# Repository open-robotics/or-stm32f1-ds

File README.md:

OR-STM32F1-DS
=============

Open Robotics controller based on STM32F103VC chip.

Feauters
--------

* 20 servo control outputs
* 8 RoboGPIO with ADC option
* 8 RoboGPIO with servo option
* Onboard dual channel motor H-dirver
* RoboMD2 for additional external motor driver
* Onboard USB
* Separated I<sup>2</sup>C in RoboBUS and RoboI2C
* 2 quadrature encoder inputs

Connectors
----------

* 20 Servo
* 16 RoboGPIO
* 2 brush motor
* 1 RoboBUS
* 1 RoboMD2
* 1 RoboI2C
* 1 USB

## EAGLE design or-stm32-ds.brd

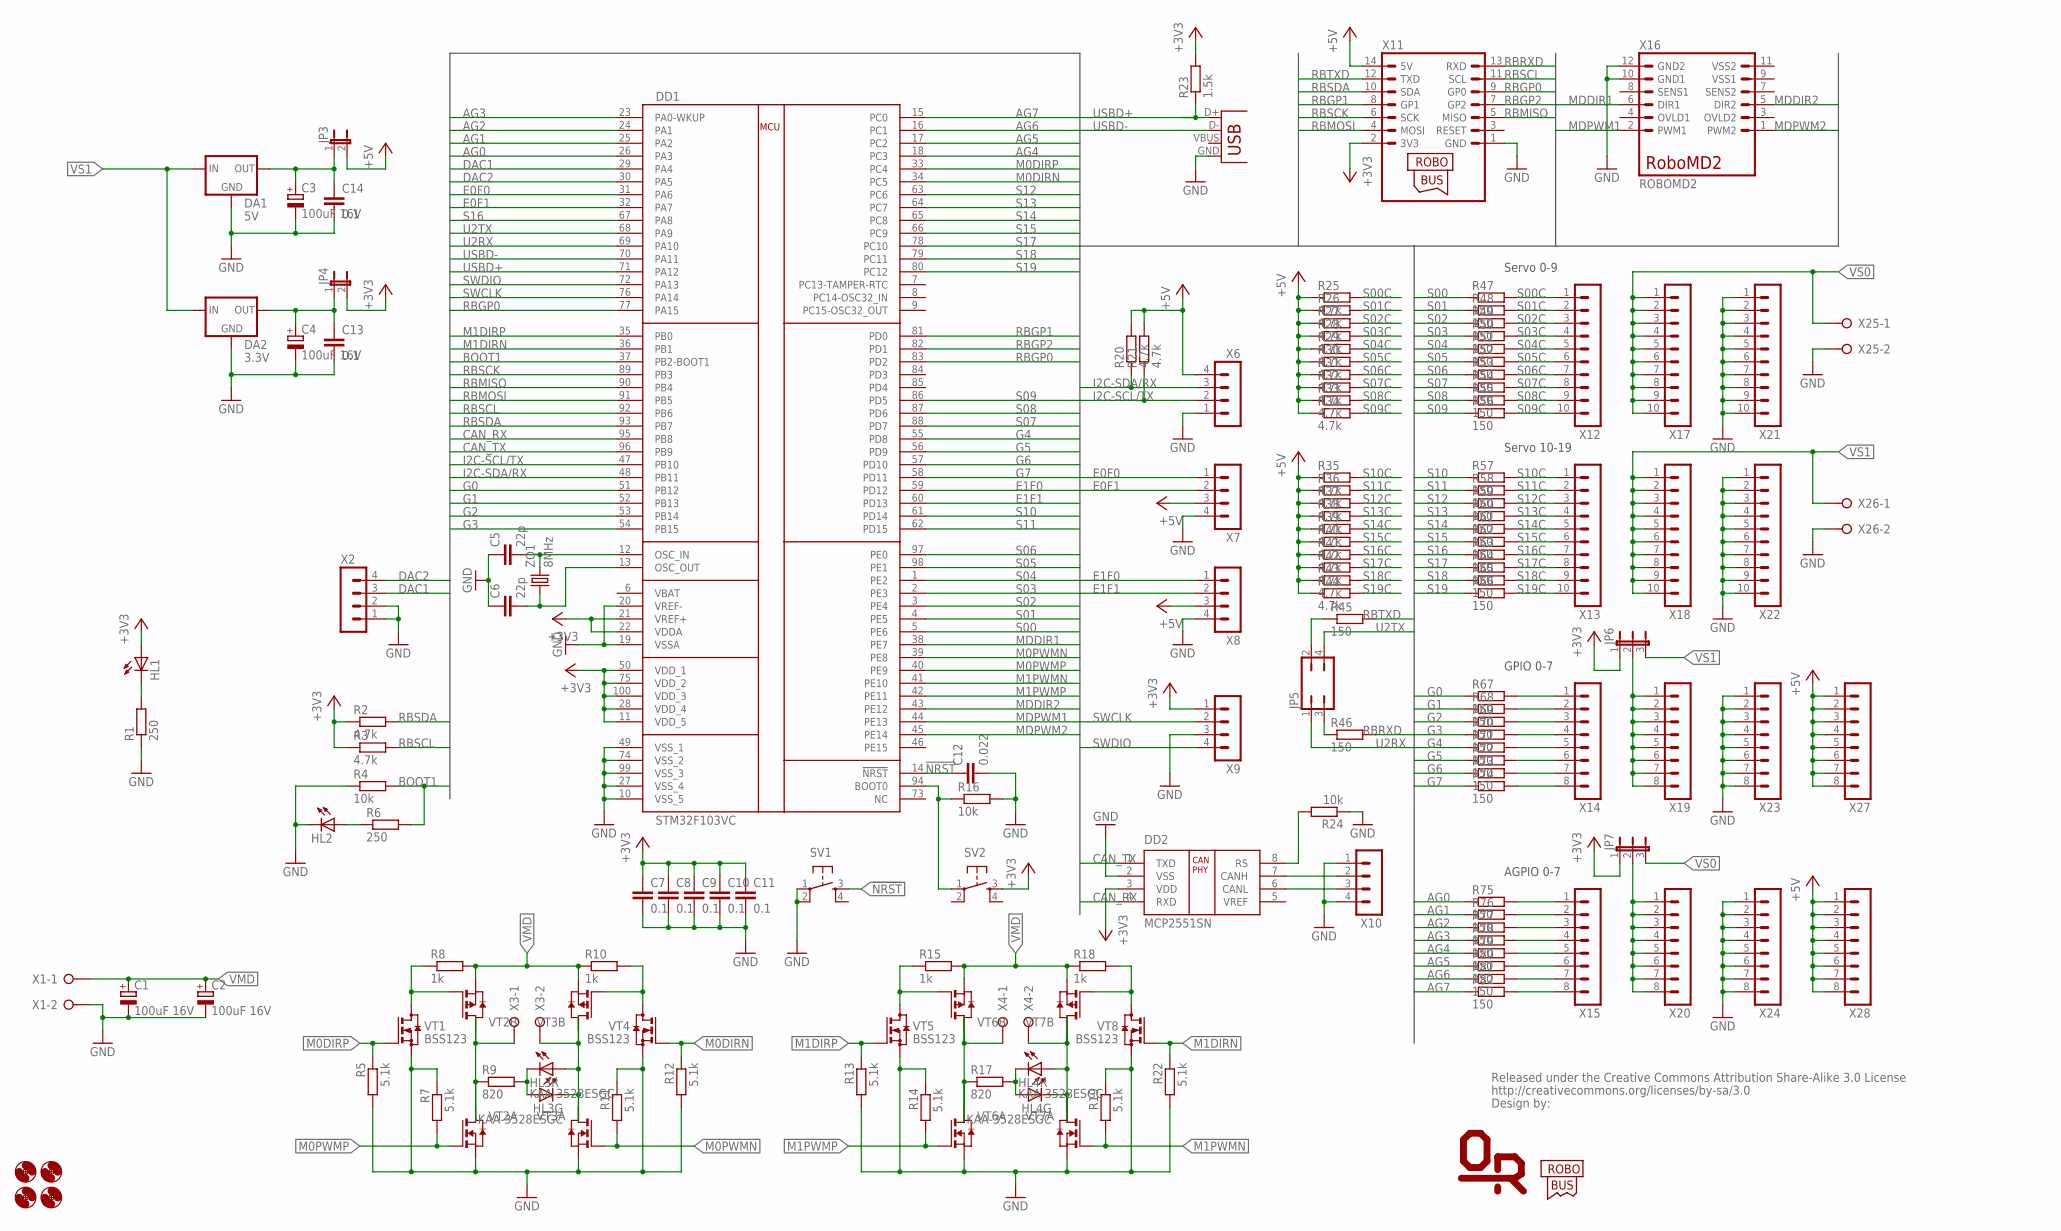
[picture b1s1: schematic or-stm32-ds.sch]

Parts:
C1, C2, C3, C4: 100uF 16V; E3,5-8
C5, C6: 22p; C0603
C7, C8, C9, C10, C11, C13, C14: 0.1; C0603
C12: 0.022; C0603
DA1: 5V; SOT223
DA2: 3.3V; SOT223
DD1: STM32F103VC; LQFP100
DD2: MCP2551SN; SO-08
H1, H2, H3, H4: MOUNT-HOLE3.2; 3,2
HL1, HL2: LEDCHIP-LED0805; CHIP-LED0805
HL3, HL4: KAA-3528ESGC; KA-3528
JP3, JP4: JP1E; JP1
JP5: JP2Q
JP6, JP7: JP2E; JP2
R1, R6: 250; R0603
R2, R3, R20, R21, R25, R26, R27, R28, R29, R30, R31, R32, R33, R34, R35, R36, R37, R38, R39, R40, R41, R42, R43, R44: 4.7k; R0603
R4, R16, R24: 10k; R0603
R5, R7, R11, R12, R13, R14, R19, R22: 5.1k; R0603
R8, R10, R15, R18: 1k; R0603
R9, R17: 820; R0603
R23: 1.5k; R0603
R45, R46, R47, R48, R49, R50, R51, R52, R53, R54, R55, R56, R57, R58, R59, R60, R61, R62, R63, R64, R65, R66, R67, R68, R69, R70, R71, R72, R73, R74, R75, R76, R77, R78, R79, R80, R81, R82: 150; R0603
SV1, SV2: TAC_SWITCHSMD; TACTILE_SWITCH_SMD
U$1: CREATIVE_COMMONS_BY-SA; CC-BY-SA-6MM
U$2: ORLOGO
U$3: ROBOBUS_LOGO
VT1, VT4, VT5, VT8: BSS123; SOT23
VT2, VT3, VT6, VT7: PN_MOSFET-SO8; SO8
X1, X3, X4: HT396R-02P
X2, X9: MA04-11.27MM; 1X04-1.27MM
X5: USBSMD; USB-MINIB
X6, X7, X8, X10: MA04-1
X11: ROBOBUSR; ML14L
X12, X13, X17, X18, X21, X22: MA10-1
X14, X15, X19, X20, X23, X24, X27, X28: MA08-1
X16: ROBOMD2; ML12
X25, X26: W237-02P; W237-132
ZQ1: 8MHz; HC49U-V

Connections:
!NRST: C12.1, DD1.14 (!NRST), SV1.3
+3V3: C7.1, C8.1, C9.1, C10.1, C11.1, DD1.11 (VDD_5), DD1.21 (VREF+), DD1.22 (VDDA), DD1.28 (VDD_4), DD1.50 (VDD_1), DD1.75 (VDD_2), DD1.100 (VDD_3), DD2.3 (VDD), HL1.A, JP4.2, JP6.1, JP7.1, R2.1, R3.1, R23.2, SV2.3, X9.1, X11.2 (3V3)
+5V: JP3.2, R20.2, R21.2, R25.1, R26.1, R27.1, R28.1, R29.1, R30.1, R31.1, R32.1, R33.1, R34.1, R35.1, R36.1, R37.1, R38.1, R39.1, R40.1, R41.1, R42.1, R43.1, R44.1, X6.4, X7.3, X8.3, X11.14 (5V), X27.1, X27.2, X27.3, X27.4, X27.5, X27.6, X27.7, X27.8, X28.1, X28.2, X28.3, X28.4, X28.5, X28.6, X28.7, X28.8
AG0: DD1.26 (PA3), R75.1
AG0C: R75.2, X15.1
AG1: DD1.25 (PA2), R76.1
AG1C: R76.2, X15.2
AG2: DD1.24 (PA1), R77.1
AG2C: R77.2, X15.3
AG3: DD1.23 (PA0-WKUP), R78.1
AG3C: R78.2, X15.4
AG4: DD1.18 (PC3), R79.1
AG4C: R79.2, X15.5
AG5: DD1.17 (PC2), R80.1
AG5C: R80.2, X15.6
AG6: DD1.16 (PC1), R81.1
AG6C: R81.2, X15.7
AG7: DD1.15 (PC0), R82.1
AG7C: R82.2, X15.8
BOOT0: DD1.94 (BOOT0), R16.1, SV2.1
BOOT1: DD1.37 (PB2-BOOT1), R4.2, R6.2
CANH: DD2.7 (CANH), X10.2
CANL: DD2.6 (CANL), X10.3
CANRS: DD2.8 (RS), R24.2
CAN_RX: DD1.95 (PB8), DD2.4 (RXD)
CAN_TX: DD1.96 (PB9), DD2.1 (TXD)
DAC1: DD1.29 (PA4), X2.3
DAC2: DD1.30 (PA5), X2.4
E0F0: DD1.31 (PA6), X7.1
E0F1: DD1.32 (PA7), X7.2
E1F0: DD1.59 (PD12), X8.1
E1F1: DD1.60 (PD13), X8.2
G0: DD1.51 (PB12), R67.1
G0C: R67.2, X14.1
G1: DD1.52 (PB13), R68.1
G1C: R68.2, X14.2
G2: DD1.53 (PB14), R69.1
G2C: R69.2, X14.3
G3: DD1.54 (PB15), R70.1
G3C: R70.2, X14.4
G4: DD1.55 (PD8), R71.1
G4C: R71.2, X14.5
G5: DD1.56 (PD9), R72.1
G5C: R72.2, X14.6
G6: DD1.57 (PD10), R73.1
G6C: R73.2, X14.7
G7: DD1.58 (PD11), R74.1
G7C: R74.2, X14.8
GND: C1.-, C2.-, C3.-, C4.-, C5.1, C6.1, C7.2, C8.2, C9.2, C10.2, C11.2, C12.2, C13.2, C14.2, DA1.1 (GND), DA2.1 (GND), DD1.10 (VSS_5), DD1.19 (VSSA), DD1.20 (VREF-), DD1.27 (VSS_4), DD1.49 (VSS_1), DD1.74 (VSS_2), DD1.99 (VSS_3), DD2.2 (VSS), HL2.C, R1.1, R4.1, R5.2, R7.1, R11.1, R12.2, R13.2, R14.1, R16.2, R19.1, R22.2, R24.1, SV1.1, SV1.2, VT1.2 (S), VT2.1 (S), VT3.1 (S), VT4.2 (S), VT5.2 (S), VT6.1 (S), VT7.1 (S), VT8.2 (S), X1.2, X2.1, X2.2, X5.GND, X6.1, X7.4, X8.4, X9.3, X10.1, X10.4, X11.1 (GND), X16.10 (GND1), X16.12 (GND2), X21.1, X21.2, X21.3, X21.4, X21.5, X21.6, X21.7, X21.8, X21.9, X21.10, X22.1, X22.2, X22.3, X22.4, X22.5, X22.6, X22.7, X22.8, X22.9, X22.10, X23.1, X23.2, X23.3, X23.4, X23.5, X23.6, X23.7, X23.8, X24.1, X24.2, X24.3, X24.4, X24.5, X24.6, X24.7, X24.8, X25.2, X26.2
GPVCC: JP6.2, X19.1, X19.2, X19.3, X19.4, X19.5, X19.6, X19.7, X19.8
I2C-SCL/TX: DD1.47 (PB10), R21.1, X6.2
I2C-SDA/RX: DD1.48 (PB11), R20.1, X6.3
M0C+: R9.1, VT2.5 (D), VT2.6 (D2), VT2.7 (D), VT2.8 (D2), X3.1
M0C+1: R17.1, VT6.5 (D), VT6.6 (D2), VT6.7 (D), VT6.8 (D2), X4.1
M0C-: HL3.2 (A), HL3.3 (C), VT3.5 (D), VT3.6 (D2), VT3.7 (D), VT3.8 (D2), X3.2
M0C-1: HL4.2 (A), HL4.3 (C), VT7.5 (D), VT7.6 (D2), VT7.7 (D), VT7.8 (D2), X4.2
M0DIRN: DD1.34 (PC5), R12.1, VT4.1 (G)
M0DIRP: DD1.33 (PC4), R5.1, VT1.1 (G)
M0PWMN: DD1.39 (PE8), R11.2, VT3.2 (G)
M0PWMP: DD1.40 (PE9), R7.2, VT2.2 (G)
M1DIRN: DD1.36 (PB1), R22.1, VT8.1 (G)
M1DIRP: DD1.35 (PB0), R13.1, VT5.1 (G)
M1PWMN: DD1.41 (PE10), R19.2, VT7.2 (G)
M1PWMP: DD1.42 (PE11), R14.2, VT6.2 (G)
MDDIR1: DD1.38 (PE7), X16.6 (DIR1)
MDDIR2: DD1.43 (PE12), X16.5 (DIR2)
MDPWM1: DD1.44 (PE13), X16.2 (PWM1)
MDPWM2: DD1.45 (PE14), X16.1 (PWM2)
unnamed: JP5.3, R46.1
unnamed: C5.2, DD1.12 (OSC_IN), ZQ1.2
unnamed: C6.2, DD1.13 (OSC_OUT), ZQ1.1
unnamed: JP7.2, X20.1, X20.2, X20.3, X20.4, X20.5, X20.6, X20.7, X20.8
unnamed: JP5.2, R45.1
unnamed: HL1.C, R1.2
unnamed: HL2.A, R6.1
unnamed: R8.1, VT1.3 (D), VT2.4 (G)
unnamed: R10.2, VT3.4 (G), VT4.3 (D)
unnamed: HL3.1 (C), HL3.4 (A), R9.2
unnamed: R15.1, VT5.3 (D), VT6.4 (G)
unnamed: R18.2, VT7.4 (G), VT8.3 (D)
unnamed: HL4.1 (C), HL4.4 (A), R17.2
RBGP0: DD1.77 (PA15), DD1.83 (PD2), X11.9 (GP0)
RBGP1: DD1.81 (PD0), X11.8 (GP1)
RBGP2: DD1.82 (PD1), X11.7 (GP2)
RBMISO: DD1.90 (PB4), X11.5 (MISO)
RBMOSI: DD1.91 (PB5), X11.4 (MOSI)
RBRXD: R46.2, X11.13 (RXD)
RBSCK: DD1.89 (PB3), X11.6 (SCK)
RBSCL: DD1.92 (PB6), R3.2, X11.11 (SCL)
RBSDA: DD1.93 (PB7), R2.2, X11.10 (SDA)
RBTXD: R45.2, X11.12 (TXD)
S00: DD1.5 (PE6), R47.1
S00C: R25.2, R47.2, X12.1
S01: DD1.4 (PE5), R48.1
S01C: R26.2, R48.2, X12.2
S02: DD1.3 (PE4), R49.1
S02C: R27.2, R49.2, X12.3
S03: DD1.2 (PE3), R50.1
S03C: R28.2, R50.2, X12.4
S04: DD1.1 (PE2), R51.1
S04C: R29.2, R51.2, X12.5
S05: DD1.98 (PE1), R52.1
S05C: R30.2, R52.2, X12.6
S06: DD1.97 (PE0), R53.1
S06C: R31.2, R53.2, X12.7
S07: DD1.88 (PD7), R54.1
S07C: R32.2, R54.2, X12.8
S08: DD1.87 (PD6), R55.1
S08C: R33.2, R55.2, X12.9
S09: DD1.86 (PD5), R56.1
S09C: R34.2, R56.2, X12.10
S10: DD1.61 (PD14), R57.1
S10C: R35.2, R57.2, X13.1
S11: DD1.62 (PD15), R58.1
S11C: R36.2, R58.2, X13.2
S12: DD1.63 (PC6), R59.1
S12C: R37.2, R59.2, X13.3
S13: DD1.64 (PC7), R60.1
S13C: R38.2, R60.2, X13.4
S14: DD1.65 (PC8), R61.1
S14C: R39.2, R61.2, X13.5
S15: DD1.66 (PC9), R62.1
S15C: R40.2, R62.2, X13.6
S16: DD1.67 (PA8), R63.1
S16C: R41.2, R63.2, X13.7
S17: DD1.78 (PC10), R64.1
S17C: R42.2, R64.2, X13.8
S18: DD1.79 (PC11), R65.1
S18C: R43.2, R65.2, X13.9
S19: DD1.80 (PC12), R66.1
S19C: R44.2, R66.2, X13.10
SWCLK: DD1.76 (PA14), X9.2
SWDIO: DD1.72 (PA13), X9.4
U2RX: DD1.69 (PA10), JP5.1
U2TX: DD1.68 (PA9), JP5.4
USBD+: DD1.71 (PA12), R23.1, X5.D+
USBD-: DD1.70 (PA11), X5.D-
VMD: C1.+, C2.+, R8.2, R10.1, R15.2, R18.1, VT2.3 (S), VT3.3 (S), VT6.3 (S), VT7.3 (S), X1.1
VREF: DD2.5 (VREF)
VREG5: C3.+, C14.1, DA1.2 (OUT), JP3.1
VREG33: C4.+, C13.1, DA2.2 (OUT), JP4.1
VS0: JP7.3, X17.1, X17.2, X17.3, X17.4, X17.5, X17.6, X17.7, X17.8, X17.9, X17.10, X25.1
VS1: DA1.3 (IN), DA2.3 (IN), JP6.3, X18.1, X18.2, X18.3, X18.4, X18.5, X18.6, X18.7, X18.8, X18.9, X18.10, X26.1

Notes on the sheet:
Servo 0-9
Servo 10-19
GPIO 0-7
AGPIO 0-7

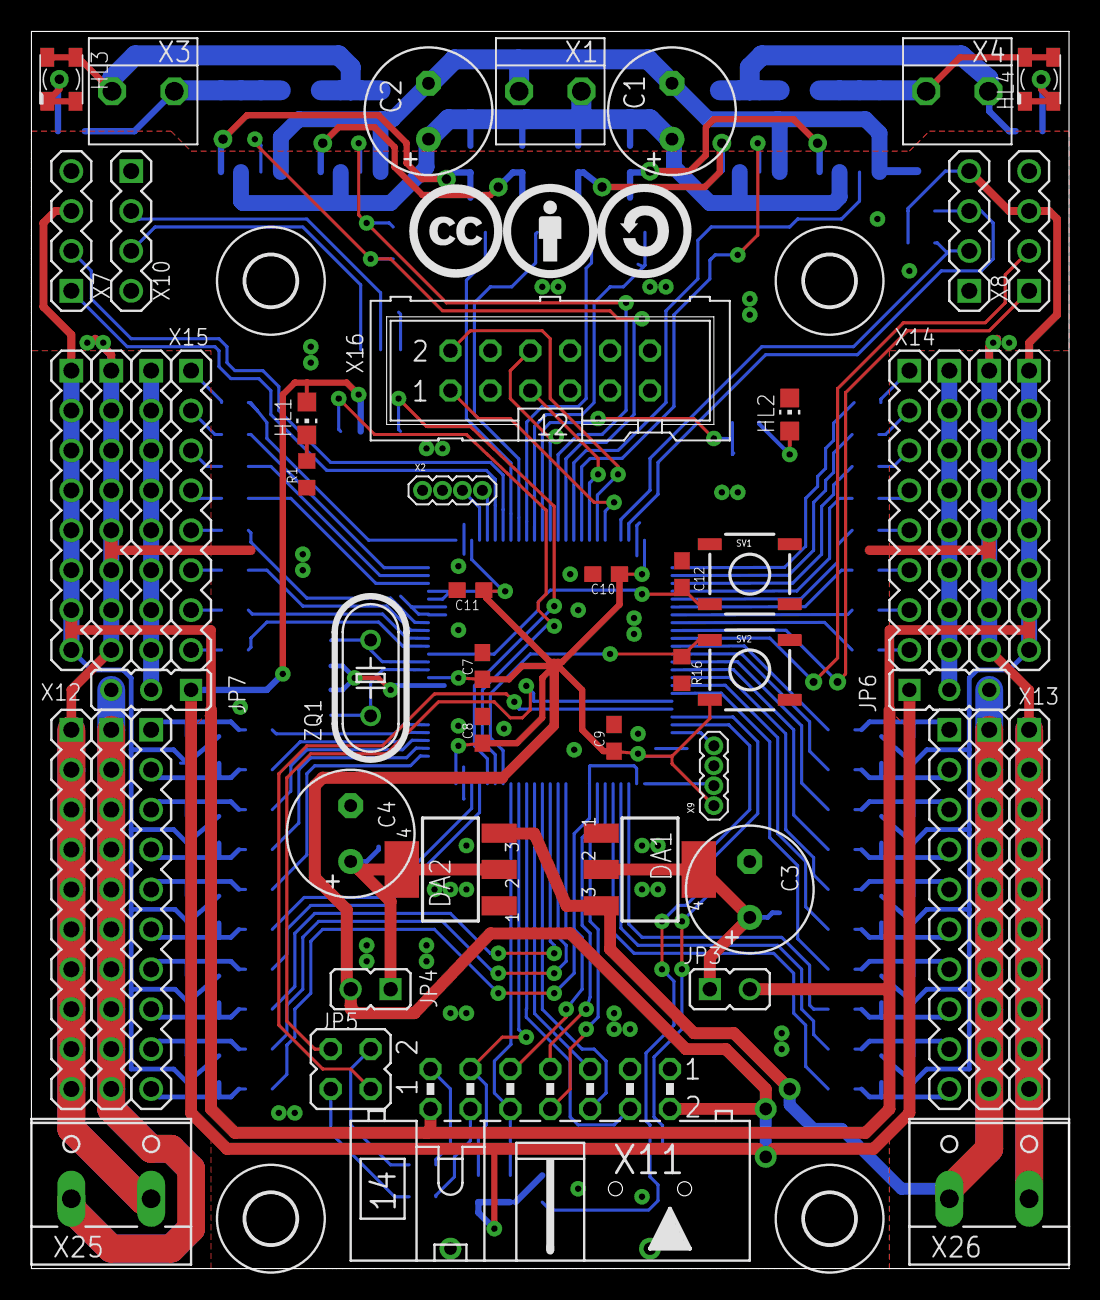
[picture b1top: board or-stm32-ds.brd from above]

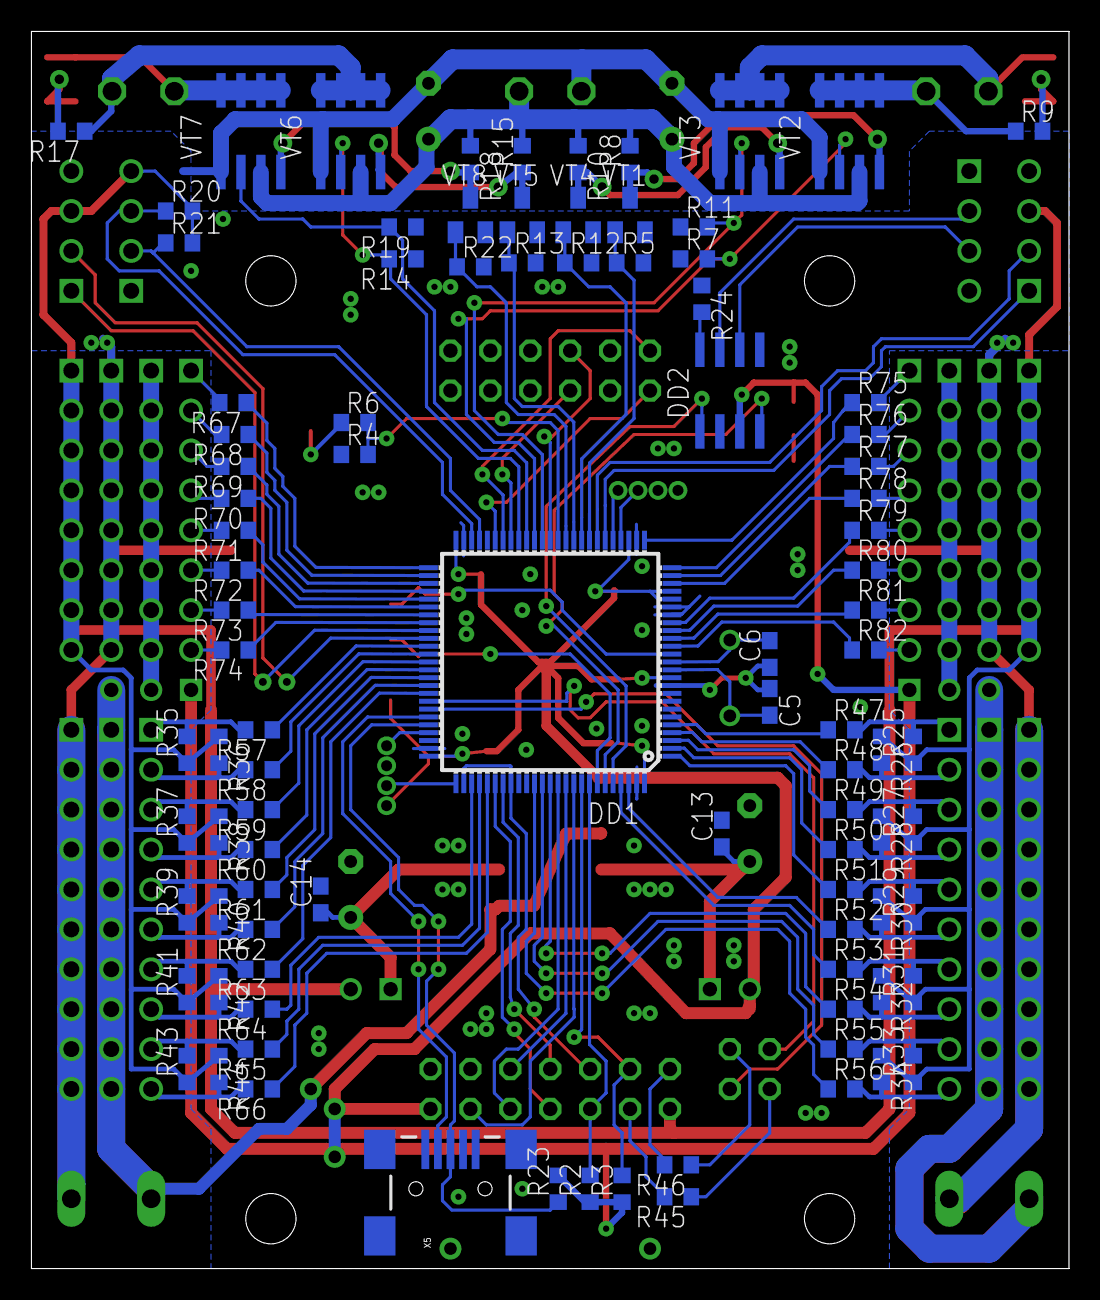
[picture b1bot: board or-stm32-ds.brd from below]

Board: 2 copper layers, 66.0 x 78.7 mm, 155 parts (95 on the bottom side), 142 nets.

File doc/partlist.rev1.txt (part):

Partlist

Exported from or-stm32-ds.sch at 01.11.11 23:47

EAGLE Version 5.11.0 Copyright (c) 1988-2010 CadSoft

Part     Value          Device          Package            Library                 Sheet

C1       100uF 16V      CPOL-EUE3.5-8   E3,5-8             rcl                     1
C2       100uF 16V      CPOL-EUE3.5-8   E3,5-8             rcl                     1
C3       100uF 16V      CPOL-EUE3.5-8   E3,5-8             rcl                     1
C4       100uF 16V      CPOL-EUE3.5-8   E3,5-8             rcl                     1
C5       22p            C-EUC0603       C0603              rcl                     1
C6       22p            C-EUC0603       C0603              rcl                     1
C7       0.1            C-EUC0603       C0603              rcl                     1
C8       0.1            C-EUC0603       C0603              rcl                     1
C9       0.1            C-EUC0603       C0603              rcl                     1
C10      0.1            C-EUC0603       C0603              rcl                     1
C11      0.1            C-EUC0603       C0603              rcl                     1
C12      0.022          C-EUC0603       C0603              rcl                     1
C13      0.1            C-EUC0603       C0603              rcl                     1
C14      0.1            C-EUC0603       C0603              rcl                     1
DA1      5V             LM1117          SOT223             v-reg-3                 1
DA2      3.3V           LM1117          SOT223             v-reg-3                 1
DD1      STM32F103VC    STM32F103VC     LQFP100            stm32f103               1
DD2      MCP2551SN      MCP2551SN       SO-08              can                     1
HL1                     LEDCHIP-LED0805 CHIP-LED0805       led                     1
HL2                     LEDCHIP-LED0805 CHIP-LED0805       led                     1
HL3      KAA-3528ESGC   KAA-3528ESGC    KA-3528            led2                    1
HL4      KAA-3528ESGC   KAA-3528ESGC    KA-3528            led2                    1
JP3                     JP1E            JP1                con-std                 1
JP4                     JP1E            JP1                con-std                 1
JP5                     JP2Q            JP2Q               jumper                  1
JP6                     JP2E            JP2                con-std                 1
JP7                     JP2E            JP2                con-std                 1
R1       250            R-EU_R0603      R0603              rcl                     1
R2       4.7k           R-EU_R0603      R0603              rcl                     1
R3       4.7k           R-EU_R0603      R0603              rcl                     1
R4       10k            R-EU_R0603      R0603              rcl                     1
R5       5.1k           R-EU_R0603      R0603              rcl                     1
R6       250            R-EU_R0603      R0603              rcl                     1
R7       5.1k           R-EU_R0603      R0603              rcl                     1
R8       1k             R-EU_R0603      R0603              rcl                     1
R9       820            R-EU_R0603      R0603              rcl                     1
R10      1k             R-EU_R0603      R0603              rcl                     1
R11      5.1k           R-EU_R0603      R0603              rcl                     1
R12      5.1k           R-EU_R0603      R0603              rcl                     1
R13      5.1k           R-EU_R0603      R0603              rcl                     1
R14      5.1k           R-EU_R0603      R0603              rcl                     1
R15      1k             R-EU_R0603      R0603              rcl                     1
R16      10k            R-EU_R0603      R0603              rcl                     1
R17      820            R-EU_R0603      R0603              rcl                     1
R18      1k             R-EU_R0603      R0603              rcl                     1
R19      5.1k           R-EU_R0603      R0603              rcl                     1
R20      4.7k           R-EU_R0603      R0603              rcl                     1
R21      4.7k           R-EU_R0603      R0603              rcl                     1
R22      5.1k           R-EU_R0603      R0603              rcl                     1
R23      1.5k           R-EU_R0603      R0603              rcl                     1
R24      10k            R-EU_R0603      R0603              rcl                     1
R25      4.7k           R-EU_R0603      R0603              rcl                     1
R26      4.7k           R-EU_R0603      R0603              rcl                     1
R27      4.7k           R-EU_R0603      R0603              rcl                     1
R28      4.7k           R-EU_R0603      R0603              rcl                     1
R29      4.7k           R-EU_R0603      R0603              rcl                     1
R30      4.7k           R-EU_R0603      R0603              rcl                     1
R31      4.7k           R-EU_R0603      R0603              rcl                     1
R32      4.7k           R-EU_R0603      R0603              rcl                     1
R33      4.7k           R-EU_R0603      R0603              rcl                     1
R34      4.7k           R-EU_R0603      R0603              rcl                     1
R35      4.7k           R-EU_R0603      R0603              rcl                     1
R36      4.7k           R-EU_R0603      R0603              rcl                     1
R37      4.7k           R-EU_R0603      R0603              rcl                     1
R38      4.7k           R-EU_R0603      R0603              rcl                     1
R39      4.7k           R-EU_R0603      R0603              rcl                     1
R40      4.7k           R-EU_R0603      R0603              rcl                     1
R41      4.7k           R-EU_R0603      R0603              rcl                     1
R42      4.7k           R-EU_R0603      R0603              rcl                     1
R43      4.7k           R-EU_R0603      R0603              rcl                     1
R44      4.7k           R-EU_R0603      R0603              rcl                     1
R45      150            R-EU_R0603      R0603              rcl                     1
R46      150            R-EU_R0603      R0603              rcl                     1
R47      150            R-EU_R0603      R0603              rcl                     1
R48      150            R-EU_R0603      R0603              rcl                     1
R49      150            R-EU_R0603      R0603              rcl                     1
R50      150            R-EU_R0603      R0603              rcl                     1
R51      150            R-EU_R0603      R0603              rcl                     1
R52      150            R-EU_R0603      R0603              rcl                     1
R53      150            R-EU_R0603      R0603              rcl                     1
R54      150            R-EU_R0603      R0603              rcl                     1
R55      150            R-EU_R0603      R0603              rcl                     1
R56      150            R-EU_R0603      R0603              rcl                     1
R57      150            R-EU_R0603      R0603              rcl                     1
R58      150            R-EU_R0603      R0603              rcl                     1
R59      150            R-EU_R0603      R0603              rcl                     1
R60      150            R-EU_R0603      R0603              rcl                     1
R61      150            R-EU_R0603      R0603              rcl                     1
R62      150            R-EU_R0603      R0603              rcl                     1
R63      150            R-EU_R0603      R0603              rcl                     1
R64      150            R-EU_R0603      R0603              rcl                     1
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
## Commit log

2011-07-02 initial. import robobus & stm32f103 library
2011-07-03 add RoboMD2-10P
2011-07-03 lower case
    --HG--
    rename : RoboBus.lbr => robobus.lbr
2011-07-19 add bolock diagram
2011-07-19 add standard RoboMD2
2011-07-19 initial add sch
2011-07-20 add frame
2011-07-20 add servo connectors
2011-07-20 add servo resistors
2011-07-23 add GPIO and AGPIO headers
2011-07-23 first pinout placement
2011-07-23 replace RoboMD2-10P to RoboMD2
2011-07-23 add USB, encoders
2011-07-23 add CAN lib
2011-07-23 add CAN
2011-07-23 change jumper pads
2011-07-23 move gpio
2011-07-26 edit descr
2011-07-28 move connectors; reconnect servo pullup's
2011-07-30 add 3.96 srew terminal
2011-07-30 add LED2 lib
2011-07-30 led2.lbr: fixup name and pads
2011-07-30 add MD. Not completed
2011-07-30 MD switch to 4-wire mode. Remove unneded logic
2011-07-30 renumber sch
2011-07-30 connect USB, CAN, ext I2C
2011-07-30 connect TIM1
2011-07-31 add rezonit.ru dru; better place for servo pull-up's (thanks =DeaD=); connect AGPIO
2011-07-31 connect I2C, SPI, UART of RoboBus
2011-07-31 connect GPIO; almost connected servo
2011-07-31 connect 2-nd pad on MOSFEET's
2011-08-01 update devmap
2011-08-06 Add logo lbr. Add CC-BY-SA logos.
2011-08-06 Connect all servo; Add power supply; License CC-BY-SA
2011-08-06 route servo, gpio, agpio, md2
2011-08-06 route all servo, power supply
2011-08-06 first route sprint done
2011-08-06 Add gerber.cam; Add silk markers
2011-08-06 FIX: wrong polarity on servo supply!
2011-08-13 Add PCB4U dru
2011-08-13 Board complete. Rev. 0
2011-08-13 Relese Rev. 0
    --HG--
    rename : devmapping.txt => doc/devmapping.txt
2011-08-13 Added tag rev.0 for changeset 37ef692d1653
2011-11-01 Fix bugs, release Rev.1
2011-11-01 add documentation for rev.1
    --HG--
    rename : doc/netlist.txt => doc/netlist.rev0.txt
    rename : doc/partlist.txt => doc/partlist.rev0.txt
    rename : doc/pinlist.txt => doc/pinlist.rev0.txt
2011-11-01 gerber files for rev.1
2011-11-01 Added tag rev.1 for changeset 7609e55cc0b1
2012-07-19 Convert to Eagle 6 XML format
2012-07-19 Add README fot github
